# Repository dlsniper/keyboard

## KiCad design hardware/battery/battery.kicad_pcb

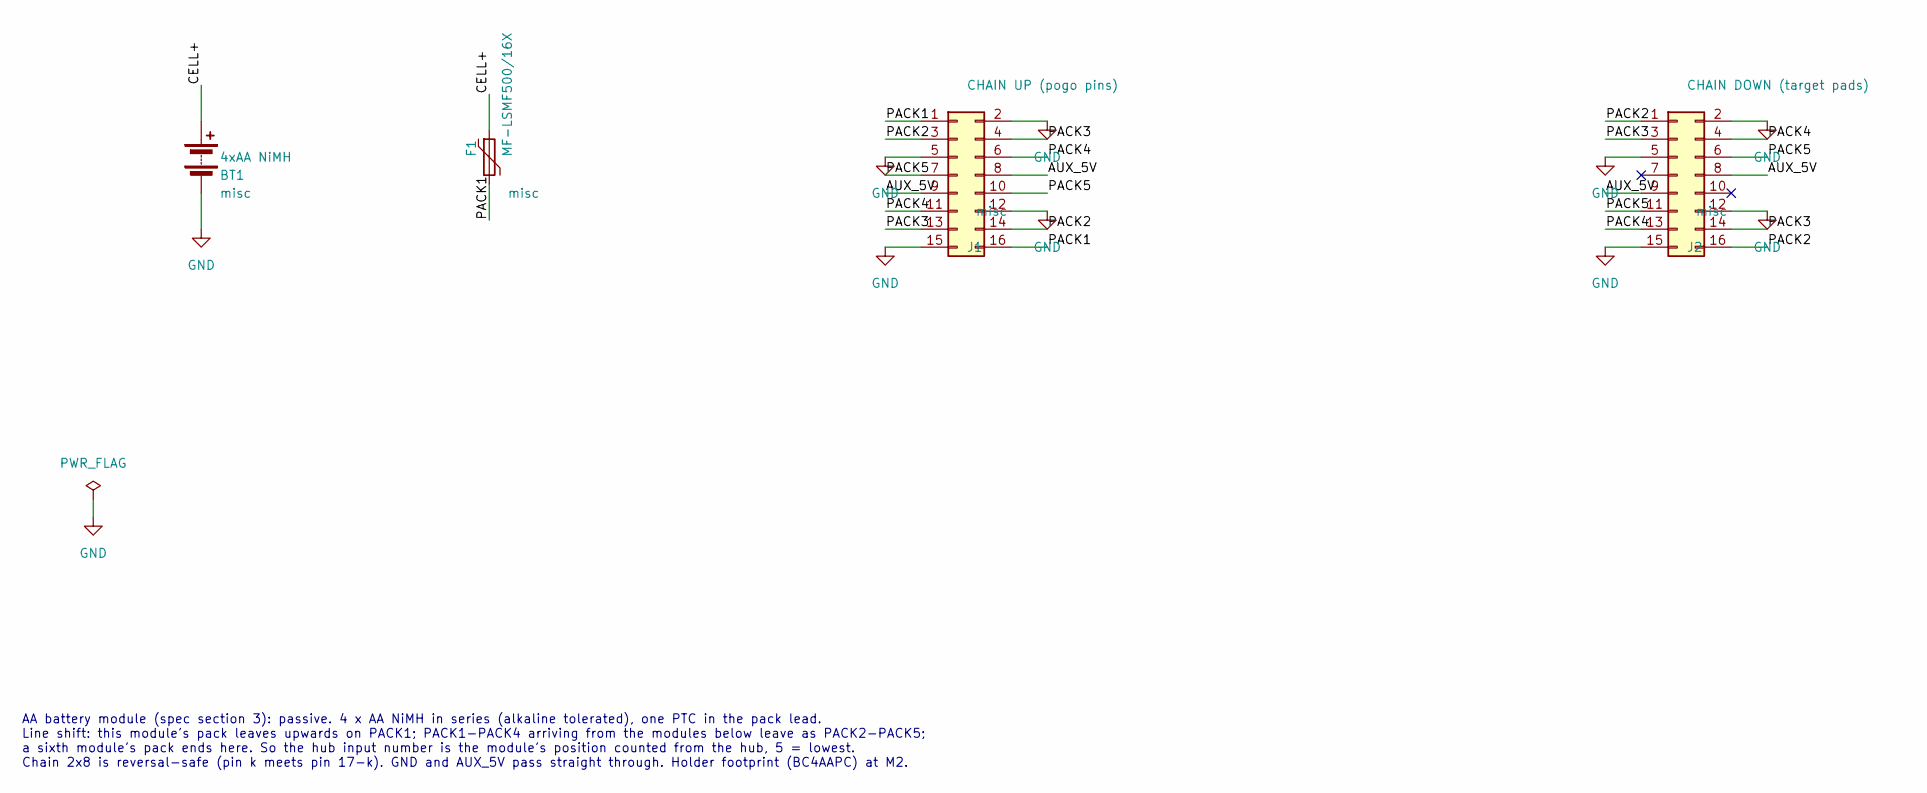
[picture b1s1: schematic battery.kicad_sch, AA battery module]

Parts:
BT1: 4xAA NiMH; BatteryHolder_MPD_BC4AAPC_4xAA; MPN MPD BC4AAPC
F1: MF-LSMF500/16X; Fuse_2920_7451Metric_Pad2.10x5.45mm_HandSolder; MPN Bourns MF-LSMF500/16X-2
J1: CHAIN UP (pogo pins); PinHeader_2x08_P2.54mm_Vertical; MPN Samtec DW-08-17-T-D-254 riser to the ca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
J2: CHAIN DOWN (target pads); PogoTarget_2x08_P2.54mm; MPN 16 x Mill-Max 1578-0-57-15-00-00-03-0 t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

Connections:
/AUX_5V: J1.8, J1.9, J2.8, J2.9
/CELL+: BT1.1 (+), F1.1
/PACK1: F1.2, J1.1, J1.16
/PACK2: J1.3, J1.14, J2.1, J2.16
/PACK3: J1.4, J1.13, J2.3, J2.14
/PACK4: J1.6, J1.11, J2.4, J2.13
/PACK5: J1.7, J1.10, J2.6, J2.11
GND: BT1.2 (-), J1.2, J1.5, J1.12, J1.15, J2.2, J2.5, J2.12, J2.15

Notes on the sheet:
AA battery module (spec section 3): passive. 4 x AA NiMH in series (alkaline tolerated), one PTC in the pack lead. Line shift: this module's pack leaves upwards on PACK1; PACK1-PACK4 arriving from the modules below leave as PACK2-PACK5; a sixth module's pack ends here. So the hub input number is th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

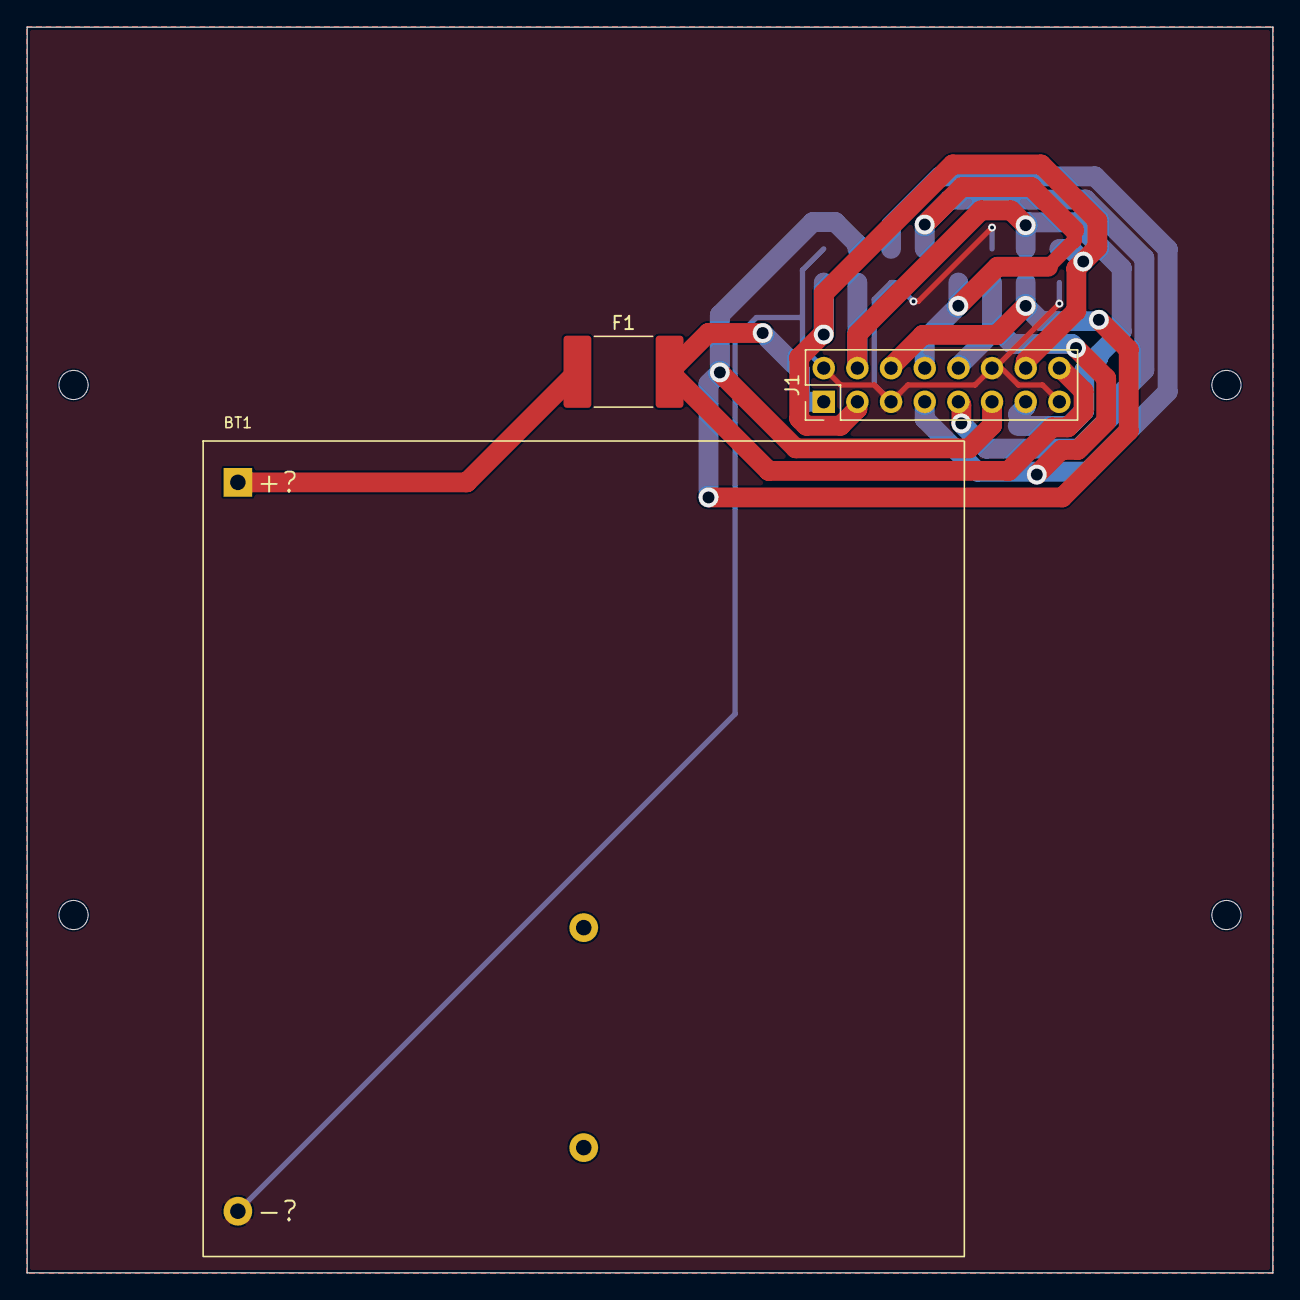
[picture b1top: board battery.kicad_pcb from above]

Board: 2 copper layers, 94.0 x 94.0 mm, 8 parts (1 on the bottom side), 8 nets.

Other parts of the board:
H1, H2, H3, H4: MountingHole_2.2mm_M2

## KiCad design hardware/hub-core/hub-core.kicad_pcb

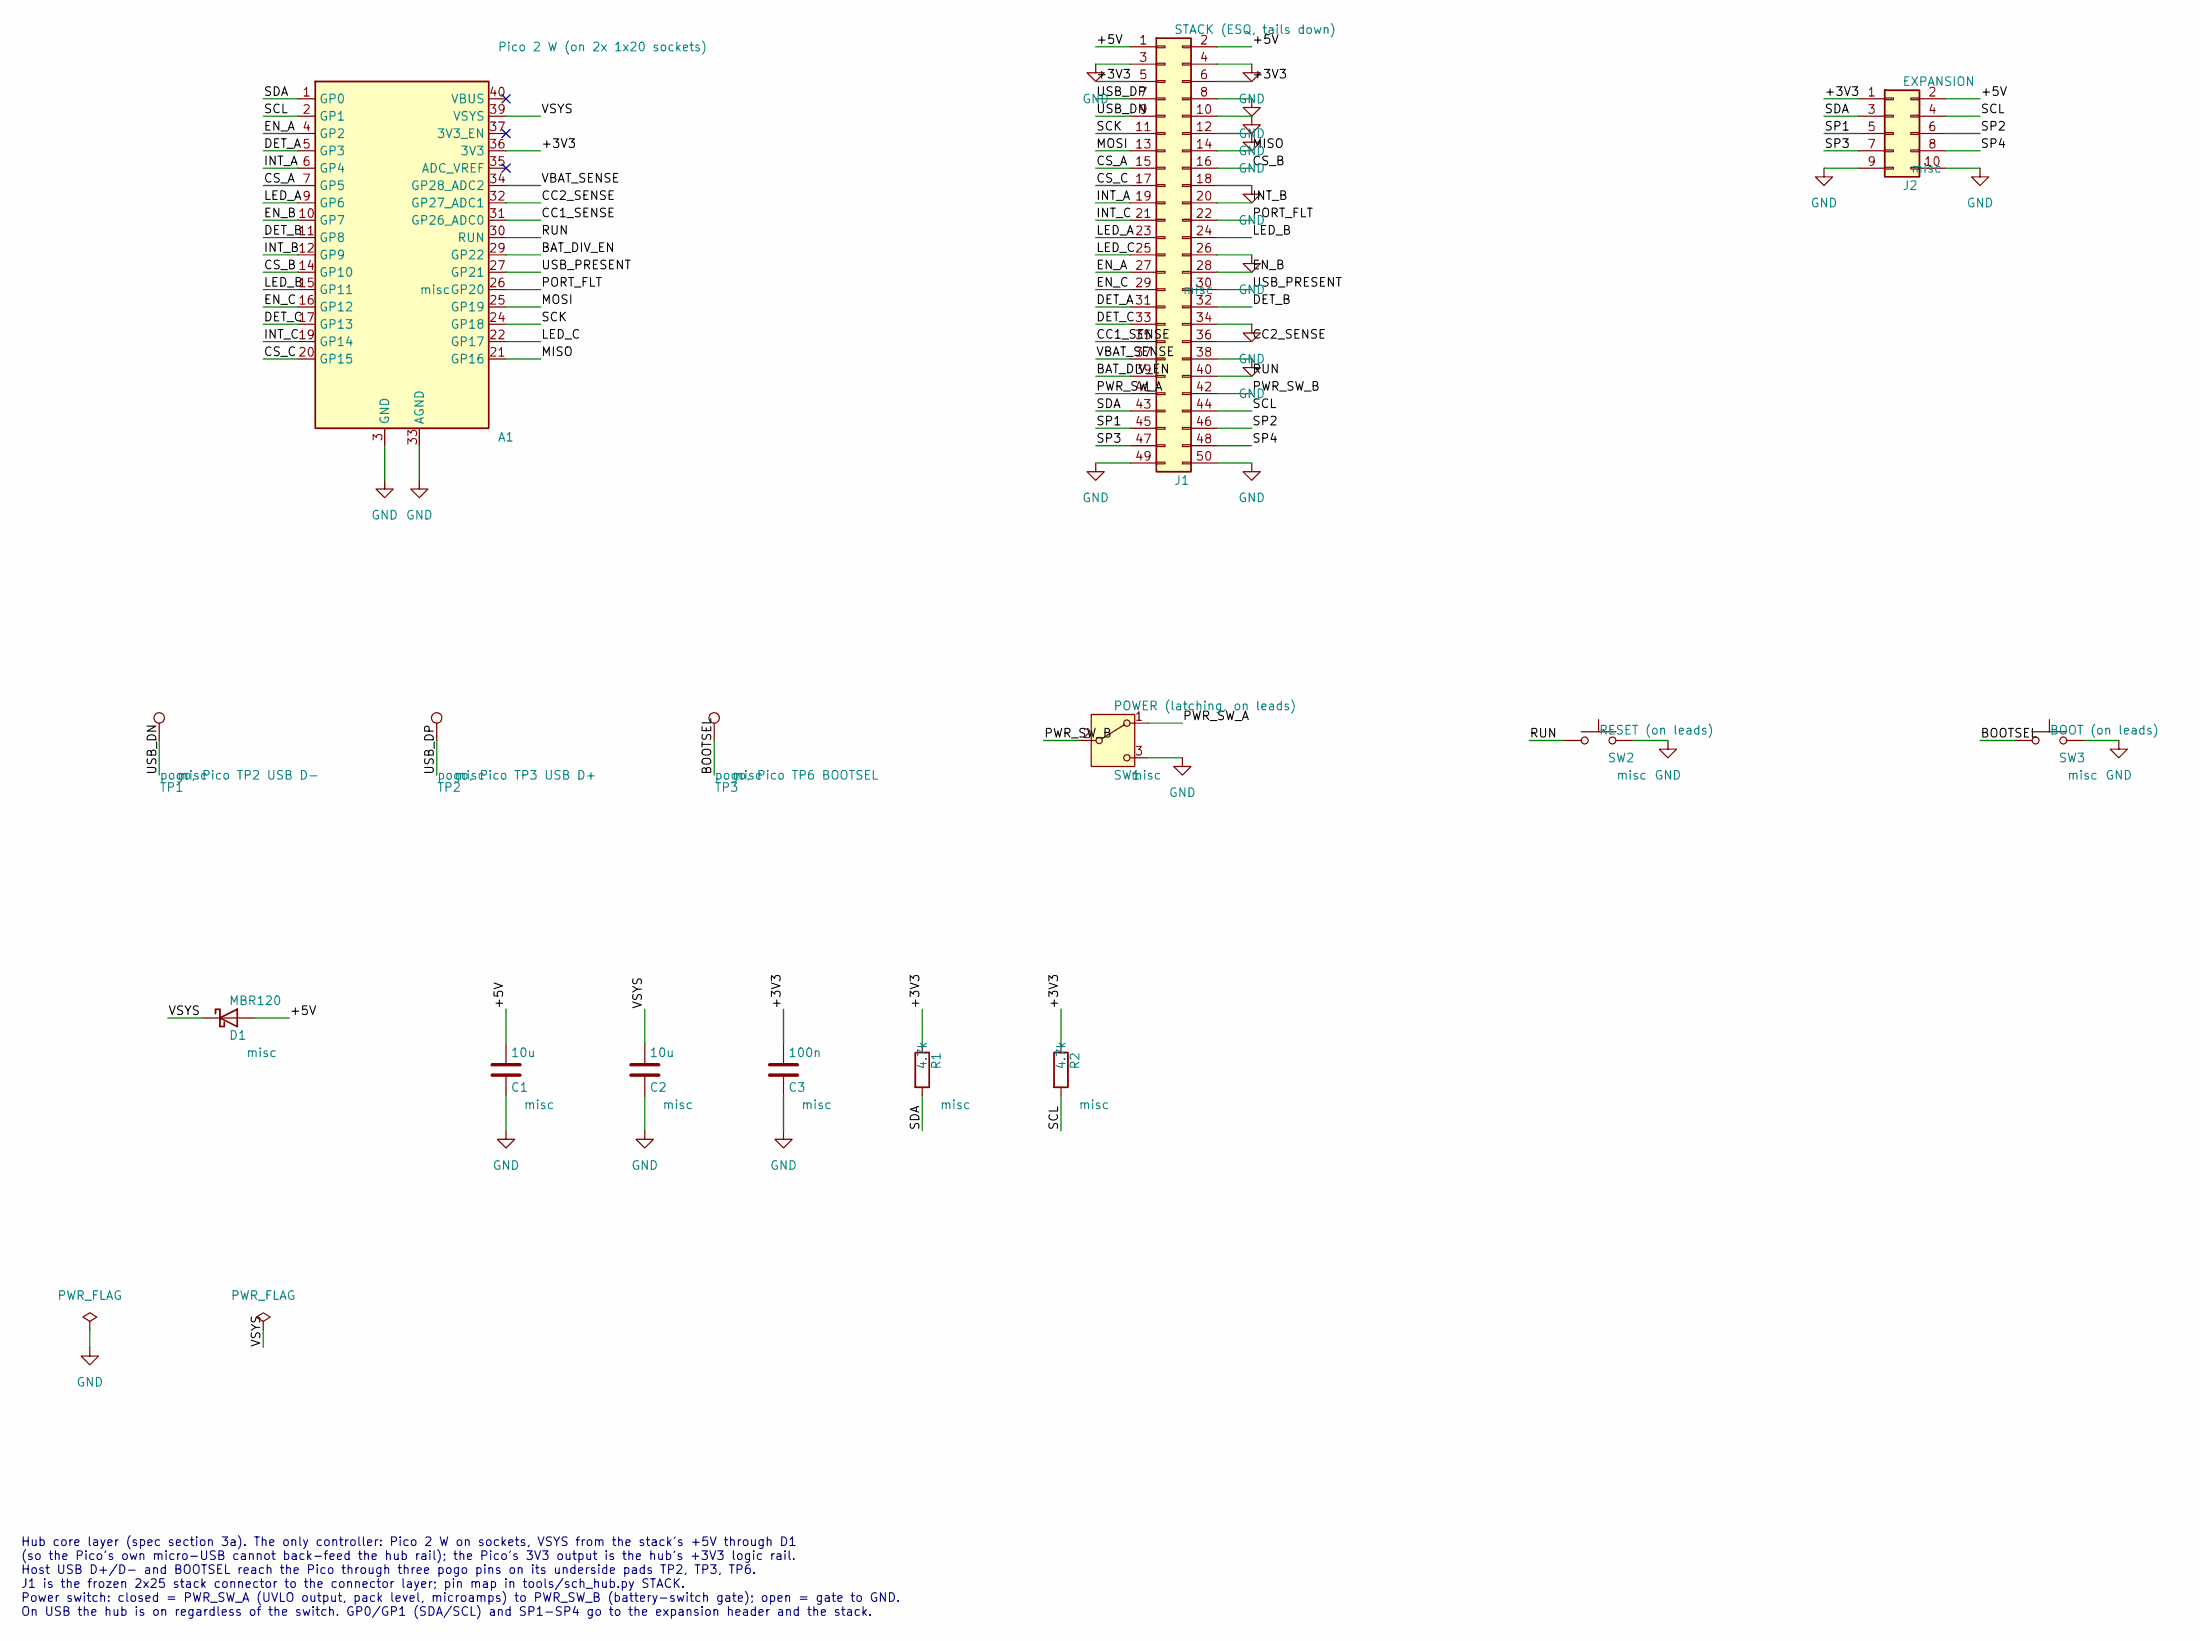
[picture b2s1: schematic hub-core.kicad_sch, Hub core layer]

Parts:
A1: Pico 2 W (on 2x 1x20 sockets); RaspberryPi_Pico_Common_THT; MPN Raspberry Pi Pico 2 W (SC1634) on 2 x 1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
C1, C2: 10u; C_0805_2012Metric_Pad1.18x1.45mm_HandSolder; Voltage 16V
C3: 100n; C_0805_2012Metric_Pad1.18x1.45mm_HandSolder; Voltage 16V
D1: MBR120; D_SOD-123; MPN onsemi MBR120VLSFT1G
J1: STACK (ESQ, tails down); PinSocket_2x25_P2.54mm_Vertical; MPN Samtec ESQ-125-24-T-D (stack-through: b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
J2: EXPANSION; PinHeader_2x05_P2.54mm_Vertical; MPN generic 2x5 2.54 mm header
R1, R2: 4.7k; R_0805_2012Metric_Pad1.20x1.40mm_HandSolder; Tolerance 1%
SW1: POWER (latching, on leads); JST_XH_B3B-XH-A_1x03_P2.50mm_Vertical; MPN NKK UB16KKG01N-F on leads to a JST XHP-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
SW2: RESET (on leads); JST_XH_B2B-XH-A_1x02_P2.50mm_Vertical; MPN NKK UB15KKG01N-C on leads to a JST XHP-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
SW3: BOOT (on leads); JST_XH_B2B-XH-A_1x02_P2.50mm_Vertical; MPN NKK UB15KKG01N-C on leads to a JST XHP-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
TP1: pogo, Pico TP2 USB D-; SpringPin_MillMax_0929_THT; MPN Mill-Max 0929-7-15-20-75-14-11-0 (12.19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
TP2: pogo, Pico TP3 USB D+; SpringPin_MillMax_0929_THT; MPN Mill-Max 0929-7-15-20-75-14-11-0 (12.19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
TP3: pogo, Pico TP6 BOOTSEL; SpringPin_MillMax_0929_THT; MPN Mill-Max 0929-7-15-20-75-14-11-0 (12.19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

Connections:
/+3V3: A1.36 (3V3), C3.1, J1.5, J1.6, J2.1, R1.1, R2.1
/+5V: C1.1, D1.2 (A), J1.1, J1.2, J2.2
/BAT_DIV_EN: A1.29 (GP22), J1.39
/BOOTSEL: SW3.1, TP3.1
/CC1_SENSE: A1.31 (GP26_ADC0), J1.35
/CC2_SENSE: A1.32 (GP27_ADC1), J1.36
/CS_A: A1.7 (GP5), J1.15
/CS_B: A1.14 (GP10), J1.16
/CS_C: A1.20 (GP15), J1.17
/DET_A: A1.5 (GP3), J1.31
/DET_B: A1.11 (GP8), J1.32
/DET_C: A1.17 (GP13), J1.33
/EN_A: A1.4 (GP2), J1.27
/EN_B: A1.10 (GP7), J1.28
/EN_C: A1.16 (GP12), J1.29
/INT_A: A1.6 (GP4), J1.19
/INT_B: A1.12 (GP9), J1.20
/INT_C: A1.19 (GP14), J1.21
/LED_A: A1.9 (GP6), J1.23
/LED_B: A1.15 (GP11), J1.24
/LED_C: A1.22 (GP17), J1.25
/MISO: A1.21 (GP16), J1.14
/MOSI: A1.25 (GP19), J1.13
/PORT_FLT: A1.26 (GP20), J1.22
/PWR_SW_A: J1.41, SW1.1 (A)
/PWR_SW_B: J1.42, SW1.2 (B)
/RUN: A1.30 (RUN), J1.40, SW2.1
/SCK: A1.24 (GP18), J1.11
/SCL: A1.2 (GP1), J1.44, J2.4, R2.2
/SDA: A1.1 (GP0), J1.43, J2.3, R1.2
/SP1: J1.45, J2.5
/SP2: J1.46, J2.6
/SP3: J1.47, J2.7
/SP4: J1.48, J2.8
/USB_DN: J1.9, TP1.1
/USB_DP: J1.7, TP2.1
/USB_PRESENT: A1.27 (GP21), J1.30
/VBAT_SENSE: A1.34 (GP28_ADC2), J1.37
/VSYS: A1.39 (VSYS), C2.1, D1.1 (K)
GND: A1.3 (GND), A1.8 (GND), A1.13 (GND), A1.18 (GND), A1.23 (GND), A1.28 (GND), A1.33 (AGND), A1.38 (GND), C1.2, C2.2, C3.2, J1.3, J1.4, J1.8, J1.10, J1.12, J1.18, J1.26, J1.34, J1.38, J1.49, J1.50, J2.9, J2.10, SW1.3 (C), SW2.2, SW3.2

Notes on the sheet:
Hub core layer (spec section 3a). The only controller: Pico 2 W on sockets, VSYS from the stack's +5V through D1 (so the Pico's own micro-USB cannot back-feed the hub rail); the Pico's 3V3 output is the hub's +3V3 logic rail. Host USB D+/D- and BOOTSEL reach the Pico through three pogo pins on its 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

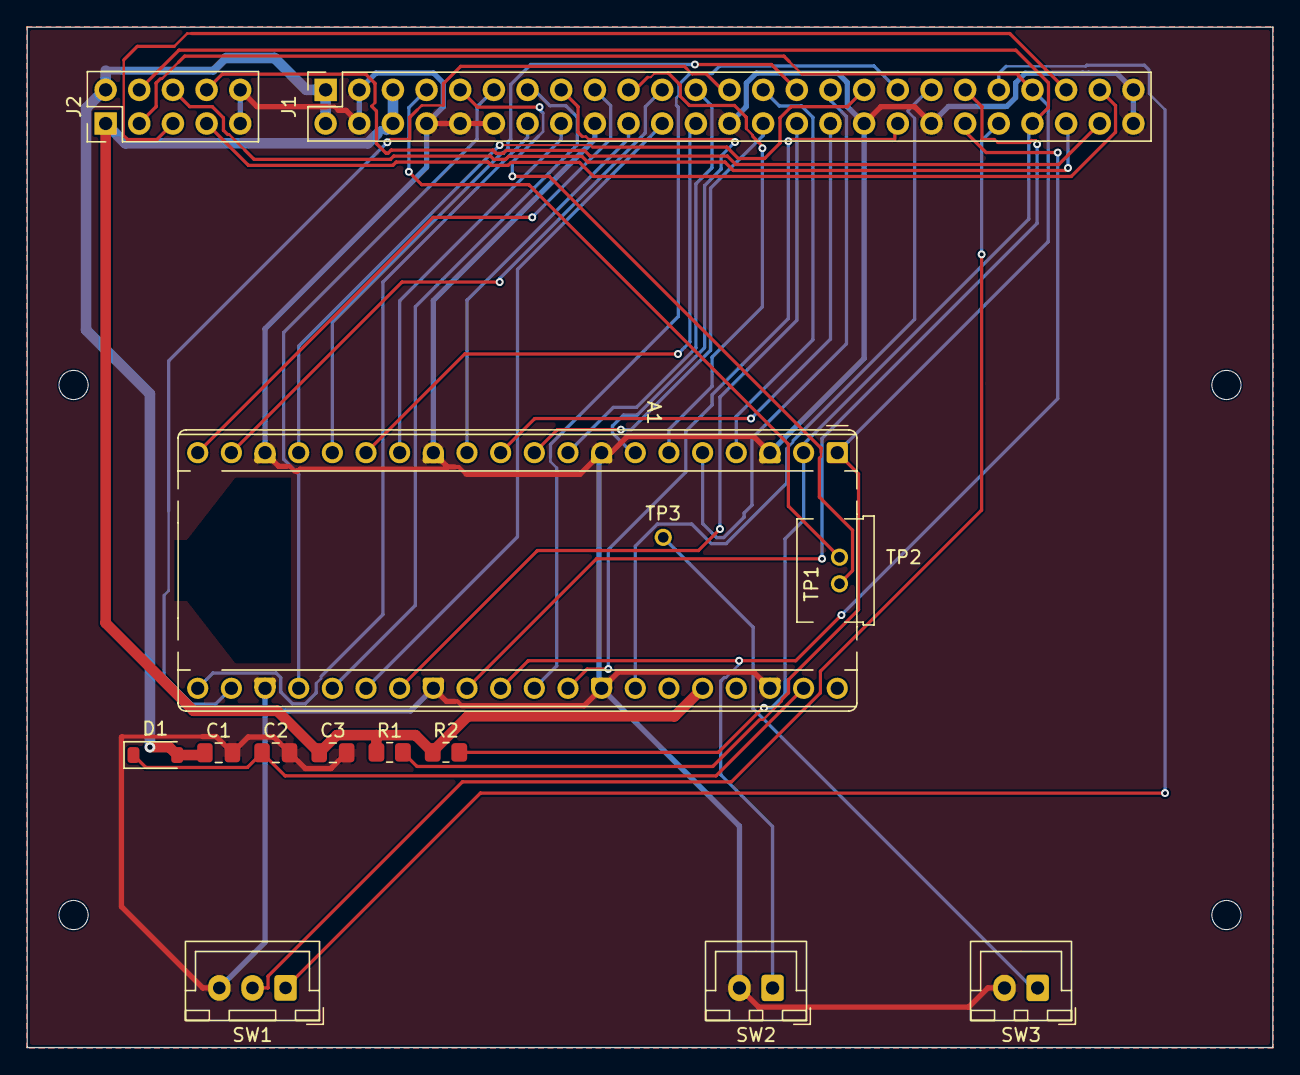
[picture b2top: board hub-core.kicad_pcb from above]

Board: 2 copper layers, 94.0 x 77.0 mm, 19 parts (0 on the bottom side), 40 nets.

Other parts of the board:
H1, H2, H3, H4: MountingHole_2.2mm_M2
